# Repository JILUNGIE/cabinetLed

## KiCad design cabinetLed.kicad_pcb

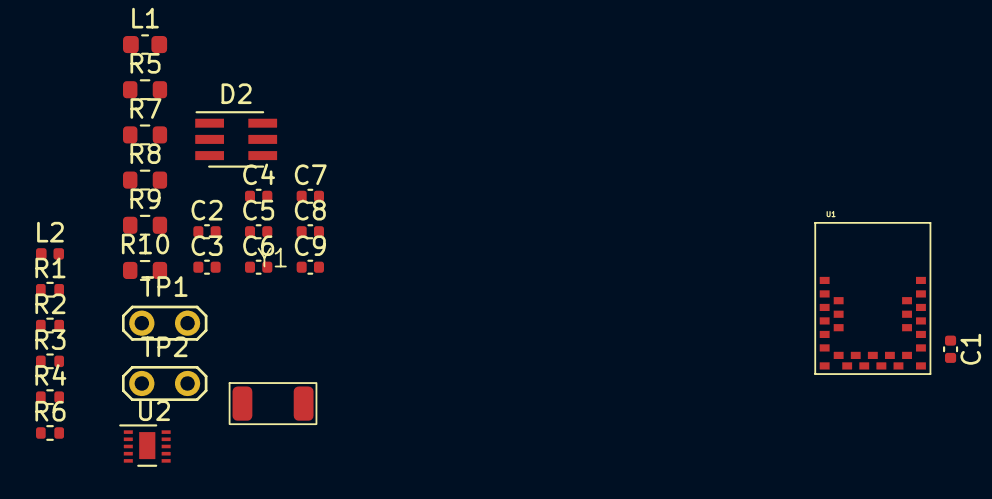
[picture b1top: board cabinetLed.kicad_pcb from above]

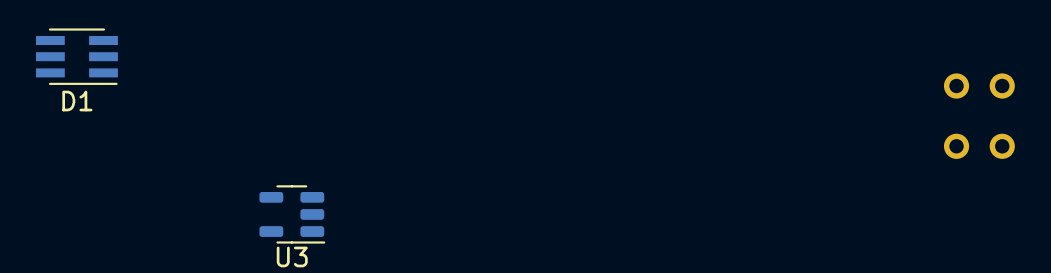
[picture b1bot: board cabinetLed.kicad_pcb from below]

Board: 2 copper layers, 31 parts (2 on the bottom side), 31 nets, no tracks yet.

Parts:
C1, C2, C4, C5, C6: 1uF/1005; C_0402_1005Metric
C3, C7: 10uF/1005; C_0402_1005Metric
C8, C9: 12pF/1005; C_0402_1005Metric
D1, D2: ASMT-YTB7-0AA02; LED_Avago_PLCC6_3x2.8mm
H1: VIN_Pad; MountingHole_2.2mm_M2
H2: BAT_Pad; MountingHole_2.2mm_M2
L1: 10uH/1608; L_0603_1608Metric
L2: 15nH/1005; L_0402_1005Metric
R1: 1K/1005; R_0402_1005Metric
R2: 5K/1005; R_0402_1005Metric
R3, R4: 10K/1005; R_0402_1005Metric
R5, R8: 24/1608; R_0603_1608Metric
R6: 3/1608; R_0402_1005Metric
R7, R9, R10: 3/1608; R_0603_1608Metric
TP1, TP2: TestPoint; TestPoint_2Pads_Pitch2.54mm_Drill0.8mm
U1: MDBT42V-512KV2; MDBT42V
U2: BQ25185; WSON-10-1EP_2.1x2.1mm_P0.4mm_EP0.9x1.5mm
U3: MIC5504-3.3YM5; SOT-23-5
Y1: DST410S

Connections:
+3V3: C6.1, C7.1, R5.1, R6.1, R7.1, R8.1, R9.1, R10.1, U1.20 (VDD), U3.5 (VOUT)
/B_BLUE: D2.1 (KB), U1.26 (P0.02)
/B_GREEN: D2.2 (KG), U1.27 (P0.03)
/B_RED: D2.3 (KR), U1.28 (P0.11)
/H_BLUE: D1.1 (KB), U1.11 (P0.09)
/H_GREEN: D1.2 (KG), U1.12 (P0.08)
/H_RED: D1.3 (KR), U1.13 (P0.10)
/STAT1: U1.6 (P0.16), U2.9 (STAT1)
/STAT2: U1.7 (P0.15), U2.3 (STAT2)
/XL1: C8.1, U1.16 (P0.00/XL1), Y1.1
/XL2: C9.1, U1.15 (P0.01/XL2), Y1.2
//CE: U1.8 (P0.14), U2.4 (/CE)
GND: C1.2, C2.2, C3.2, C4.2, C5.2, C6.2, C7.2, C8.2, C9.2, R1.2, R2.2, R3.2, U1.1 (GND), U1.10 (GND), U1.18 (GND), U1.29 (GND), U2.5 (GND), U3.2 (GND)
unnamed: D1.6 (AB), R7.2
unnamed: D1.5 (AG), R6.2
unnamed: D1.4 (AR), R5.2
unnamed: D2.6 (AB), R10.2
unnamed: D2.5 (AG), R9.2
unnamed: D2.4 (AR), R8.2
unnamed: L1.2, L2.1
unnamed: L1.1, U1.22 (DCC)
unnamed: C1.1, L2.2, U1.21 (DEC4)
unnamed: TP1.1, U1.2 (SWDCLK)
unnamed: TP2.1, U1.4 (SWDIO)
unnamed: C4.1, U2.2 (BAT)
unnamed: R2.1, U2.7 (ILIM/VSET)
unnamed: C2.1, U2.10 (IN)
unnamed: R1.1, U2.8 (ISET)
unnamed: R3.1, U2.6 (TS/MR)
unnamed: R4.2, U3.3 (EN)
VDD: C3.1, C5.1, R4.1, U2.1 (SYS), U3.1 (VIN)

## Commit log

2024-02-22 2024-02-22
2024-02-22 2024-02-22_2
2024-02-23 2024-02-23
2024-02-26 2024-02-26 change led
2024-02-28 2024-02-28
